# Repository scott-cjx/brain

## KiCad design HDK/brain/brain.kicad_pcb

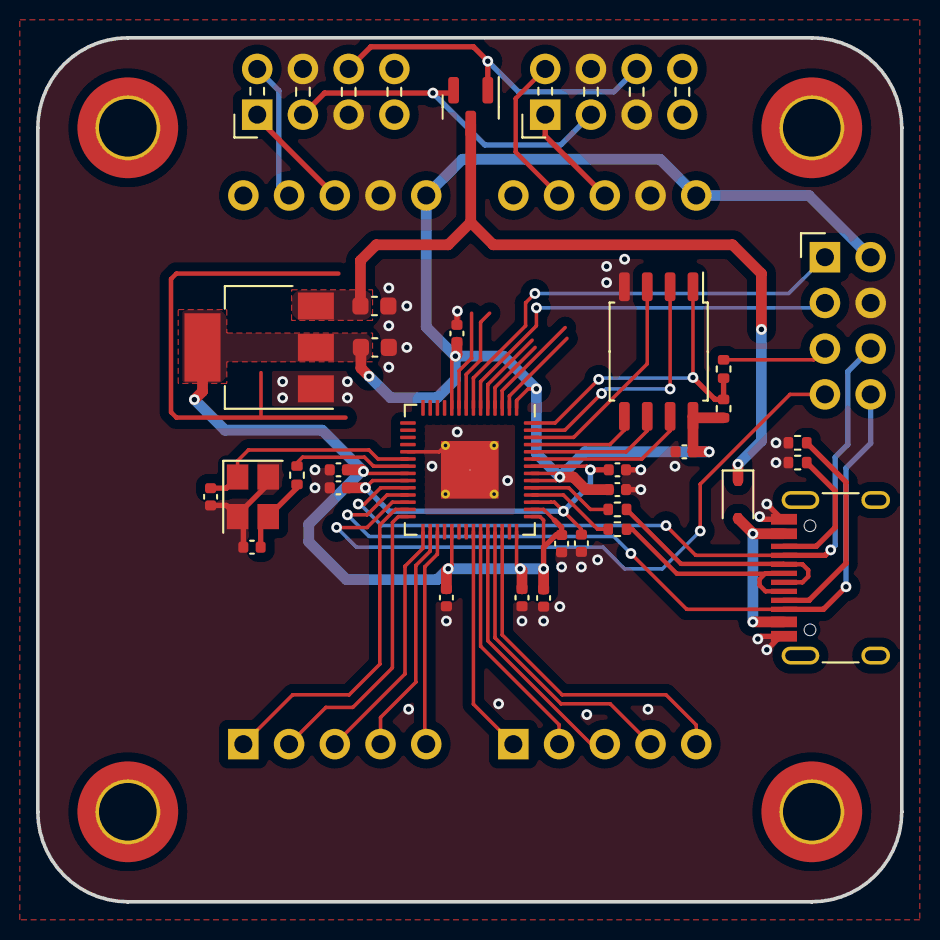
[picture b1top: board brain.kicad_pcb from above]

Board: 2 copper layers, 48.0 x 48.0 mm, 34 parts (0 on the bottom side), 42 nets.

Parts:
C201, C202, C203, C204, C205, C206, C208, C209, C211: 100n; C_0402_1005Metric
C207, C210: 1u; C_0402_1005Metric
C212, C213: 10p; C_0402_1005Metric
C401, C402: 4.7u; C_0603_1608Metric
D401: BAV70; SOT-23
D402: 1N5819WS; D_SOD-323
J301, J302: uC Interconnect; 2x04H-S
J303: DBG Connect; 2x04V-S
J304, J305: MCP251X; Can-Module-CM251X
J306: USB_C; USB_C_Receptacle_HRO_TYPE-C-31-M-12
R201, R205: 1K; R_0402_1005Metric
R202, R203: 27; R_0402_1005Metric
R204: 1K (NC); R_0402_1005Metric
R301, R302: 5k1; R_0402_1005Metric
U201: W25Q128JVS; SOIC-8_5.23x5.23mm_P1.27mm
U202: RP2040; QFN-56-1EP_7x7mm_P0.4mm_EP3.2x3.2mm_ThermalVias
U401: AMS1117-3.3; SOT-223-3_TabPin2
Y201: 12 MHz; Crystal_SMD_3225-4Pin_3.2x2.5mm

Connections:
+1V1: C208.1, C209.1, C210.1, U202.23 (DVDD), U202.45 (VREG_VOUT), U202.50 (DVDD)
+3V3: C201.1, C202.1, C203.1, C204.1, C205.1, C206.1, C207.1, C211.1, C402.1, J303.2, J304.10 (GND), J305.10 (GND), R204.1, U201.8 (VCC), U202.1 (IOVDD), U202.10 (IOVDD), U202.22 (IOVDD), U202.33 (IOVDD), U202.42 (IOVDD), U202.43 (ADC_AVDD), U202.44 (VREG_IN), U202.48 (USB_VDD), U202.49 (IOVDD), U401.2 (VO)
/CAN1_INT: J305.2 (CAN_IRQ), U202.37 (GPIO25)
/CAN2_INT: J304.2 (CAN_IRQ), U202.28 (GPIO17)
/Connectors/BOOT: J303.5, R201.2
/Connectors/CAN1_H: J301.1, J304.8 (CAN_H)
/Connectors/CAN1_L: J301.2, J304.7 (CAN_L)
/Connectors/CAN2_H: J302.1, J305.8 (CAN_H)
/Connectors/CAN2_L: J302.2, J305.7 (CAN_L)
/Connectors/SPI0_MISO: J304.5 (MISO), U202.31 (GPIO20)
/Connectors/SPI0_MOSI: J304.4 (MOSI), U202.30 (GPIO19)
/Connectors/SPI0_SCLK: J304.3 (SCK), U202.29 (GPIO18)
/Connectors/SPI1_MISO: J305.5 (MISO), U202.40 (GPIO28_ADC2)
/Connectors/SPI1_MOSI: J305.4 (MOSI), U202.39 (GPIO27_ADC1)
/Connectors/SPI1_SCLK: J305.3 (SCK), U202.38 (GPIO26_ADC0)
/Connectors/SWCLK: J303.6, J306.A8 (SBU1), U202.24 (SWCLK)
/Connectors/SWDIO: J303.8, J306.B8 (SBU2), U202.25 (SWD)
/Connectors/UART1_RX: J303.1, U202.7 (GPIO5)
/Connectors/UART1_TX: J303.3, U202.6 (GPIO4)
/Connectors/USB_DN: J306.A7 (D-), J306.B7 (D-), R203.1
/Connectors/USB_DP: J306.A6 (D+), J306.B6 (D+), R202.1
/Connectors/V_{IN1}: D401.2 (A), J301.3, J302.3
/Connectors/V_{IN2}: D401.1 (A), J301.6, J302.6
/Connectors/V_{USB}: D402.2 (A), J306.A4 (VBUS), J306.A9 (VBUS), J306.B4 (VBUS), J306.B9 (VBUS)
/Connectors/~NRST: J303.7, U202.26 (RUN)
/Controller/HSE_IN: C212.1, U202.20 (XIN), Y201.1
/Controller/HSE_OUT: C213.1, R205.1, Y201.3
/Controller/QSPI_SCLK: U201.6 (CLK), U202.52 (QSPI_SCLK)
/Controller/QSPI_SD0: U201.5 (DI(IO0)), U202.53 (QSPI_SD0)
/Controller/QSPI_SD1: U201.2 (DO(IO1)), U202.55 (QSPI_SD1)
/Controller/QSPI_SD2: U201.3 (IO2), U202.54 (QSPI_SD2)
/Controller/QSPI_SD3: U201.7 (IO3), U202.51 (QSPI_SD3)
/Controller/QSPI_SS: R201.1, R204.2, U201.1 (~CS), U202.56 (QSPI_SS)
/Controller/USB_DtN: R203.2, U202.46 (USB_DM)
/Controller/USB_DtP: R202.2, U202.47 (USB_DP)
/Power/V_{IN}: C401.1, D401.3 (K), D402.1 (K), U401.3 (VI)
/SPI0_CS1: J304.1 (~CS), U202.27 (GPIO16)
/SPI1_CS1: J305.1 (~CS), U202.36 (GPIO24)
GND: C201.2, C202.2, C203.2, C204.2, C205.2, C206.2, C207.2, C208.2, C209.2, C210.2, C211.2, C212.2, C213.2, C401.2, C402.2, J301.4, J301.5, J302.4, J302.5, J303.4, J304.9 (VCC), J305.9 (VCC), J306.A1 (GND), J306.A12 (GND), J306.B1 (GND), J306.B12 (GND), R301.2, R302.2, U201.4 (GND), U202.19 (TESTEN), U202.57 (GND), U401.1 (GND), Y201.2, Y201.4
unnamed: J306.A5 (CC1), R301.1
unnamed: J306.B5 (CC2), R302.1
unnamed: R205.2, U202.21 (XOUT)

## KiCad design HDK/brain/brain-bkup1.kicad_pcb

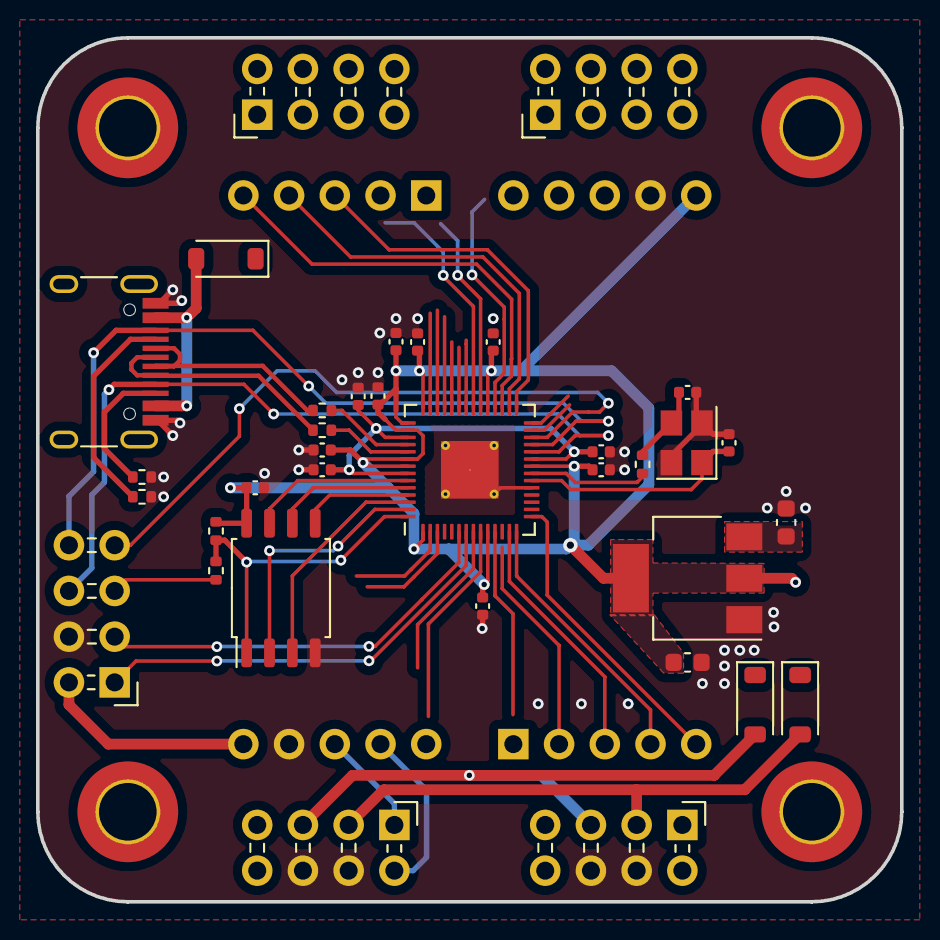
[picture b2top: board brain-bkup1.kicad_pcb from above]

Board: 2 copper layers, 48.0 x 48.0 mm, 35 parts (0 on the bottom side), 38 nets.

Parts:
C201, C202, C203, C204, C205, C206, C208, C209, C211: 100n; C_0402_1005Metric
C207, C210: 1u; C_0402_1005Metric
C212, C213: 10p; C_0402_1005Metric
C501, C502: 4.7u; C_0603_1608Metric
D501, D502, D503: D_Schottky; D_SOD-123
J301, J301#2, J305: uC Interconnect; PinHeader_2x04_P2.54mm_Horizontal
J302, J303: MCP251X; Can-Module-CM251X
J304: USB_C; USB_C_Receptacle_HRO_TYPE-C-31-M-12
R201, R205: 1K; R_0402_1005Metric
R202, R203: 27; R_0402_1005Metric
R204: 1K (NC); R_0402_1005Metric
R301, R302: 5k1; R_0402_1005Metric
U201: W25Q128JVS; SOIC-8_5.23x5.23mm_P1.27mm
U202: RP2040; QFN-56-1EP_7x7mm_P0.4mm_EP3.2x3.2mm_ThermalVias
U401: AMS1117-3.3; SOT-223-3_TabPin2
Y201: 12 MHz; Crystal_SMD_3225-4Pin_3.2x2.5mm

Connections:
+1V1: C208.1, C209.1, C210.1, U202.23 (DVDD), U202.45 (VREG_VOUT), U202.50 (DVDD)
+3V3: C201.1, C202.1, C203.1, C204.1, C205.1, C206.1, C207.1, C211.1, C502.1, J302.10 (GND), J303.10 (GND), J305.2, R204.1, U201.8 (VCC), U202.1 (IOVDD), U202.10 (IOVDD), U202.22 (IOVDD), U202.33 (IOVDD), U202.42 (IOVDD), U202.43 (ADC_AVDD), U202.44 (VREG_IN), U202.48 (USB_VDD), U202.49 (IOVDD), U401.2 (VO)
/Connectors/BOOT: J305.5, R201.2
/Connectors/CAN1_H: J301.1, J301#2.1, J302.8 (CAN_H)
/Connectors/CAN1_L: J301.2, J301#2.2, J302.7 (CAN_L)
/Connectors/IC_GP1: J301.7, J301#2.7
/Connectors/IC_GP2: J301.8, J301#2.8
/Connectors/SPI0_MISO: J302.5 (MISO), U202.31 (GPIO20)
/Connectors/SPI0_MOSI: J302.4 (MOSI), U202.30 (GPIO19)
/Connectors/SPI0_SCLK: J302.3 (SCK), U202.29 (GPIO18)
/Connectors/SPI1_MISO: J303.5 (MISO), U202.15 (GPIO12)
/Connectors/SPI1_MOSI: J303.4 (MOSI), U202.14 (GPIO11)
/Connectors/SPI1_SCLK: J303.3 (SCK), U202.13 (GPIO10)
/Connectors/SWCLK: J304.A8 (SBU1), J305.6, U202.24 (SWCLK)
/Connectors/SWDIO: J304.B8 (SBU2), J305.8, U202.25 (SWD)
/Connectors/UART1_RX: J305.1, U202.7 (GPIO5)
/Connectors/UART1_TX: J305.3, U202.6 (GPIO4)
/Connectors/USB_DN: J304.A7 (D-), J304.B7 (D-), R203.1
/Connectors/USB_DP: J304.A6 (D+), J304.B6 (D+), R202.1
/Connectors/V_{IN1}: D501.2 (A), J301.3, J301#2.3
/Connectors/V_{IN2}: D502.2 (A), J301.5, J301#2.5
/Connectors/V_{USB}: D503.2 (A), J304.A4 (VBUS), J304.A9 (VBUS), J304.B4 (VBUS), J304.B9 (VBUS)
/Connectors/~NRST: J305.7, U202.26 (RUN)
/Controller/HSE_IN: C212.1, U202.20 (XIN), Y201.1
/Controller/HSE_OUT: C213.1, R205.1, Y201.3
/Controller/QSPI_SCLK: U201.6 (CLK), U202.52 (QSPI_SCLK)
/Controller/QSPI_SD0: U201.5 (DI(IO0)), U202.53 (QSPI_SD0)
/Controller/QSPI_SD1: U201.2 (DO(IO1)), U202.55 (QSPI_SD1)
/Controller/QSPI_SD2: U201.3 (IO2), U202.54 (QSPI_SD2)
/Controller/QSPI_SD3: U201.7 (IO3), U202.51 (QSPI_SD3)
/Controller/QSPI_SS: R201.1, R204.2, U201.1 (~CS), U202.56 (QSPI_SS)
/Controller/USB_DtN: R203.2, U202.46 (USB_DM)
/Controller/USB_DtP: R202.2, U202.47 (USB_DP)
/Power/V_{IN}: C501.1, D501.1 (K), D502.1 (K), D503.1 (K), U401.3 (VI)
GND: C201.2, C202.2, C203.2, C204.2, C205.2, C206.2, C207.2, C208.2, C209.2, C210.2, C211.2, C212.2, C213.2, C501.2, C502.2, J301.4, J301.6, J301#2.4, J301#2.6, J302.9 (VCC), J303.9 (VCC), J304.A1 (GND), J304.A12 (GND), J304.B1 (GND), J304.B12 (GND), J305.4, R301.2, R302.2, U201.4 (GND), U202.19 (TESTEN), U202.57 (GND), U401.1 (GND), Y201.2, Y201.4
unnamed: J304.A5 (CC1), R301.1
unnamed: J304.B5 (CC2), R302.1
unnamed: R205.2, U202.21 (XOUT)

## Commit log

2023-11-15 Initialize gh-pages
2023-11-15 Moving files docs/* LICENSE using main
2023-11-15 Deploying to gh-pages from @ scott-cjx/brain@ebf202b23264c239323c0ee785ebfcddec2f6952 🚀
2023-12-08 updated brain wip
2023-12-08 Deploying to gh-pages from @ scott-cjx/brain@38ad701d05cce082ea9d75e95a561c7f4c9b26f7 🚀
2023-12-20 updated brain
2023-12-20 Deploying to gh-pages from @ scott-cjx/brain@3c92ba3fda96766e7c4fd15b6a15a2624687245e 🚀
